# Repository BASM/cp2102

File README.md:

cp2102
======

 Silicon Laboratories CP2102 breakout board.

 Input mini-B, output 6 pins(SIL-6): 
 * 1 -- GND
 * 2 -- Vcc(5v),
 * 3 -- RX,
 * 4 -- TX,
 * 5 -- DTR, 
 * 6 -- RTS.

 Good for NXP LPC13xx ARM programming.

 Stage: work fine.

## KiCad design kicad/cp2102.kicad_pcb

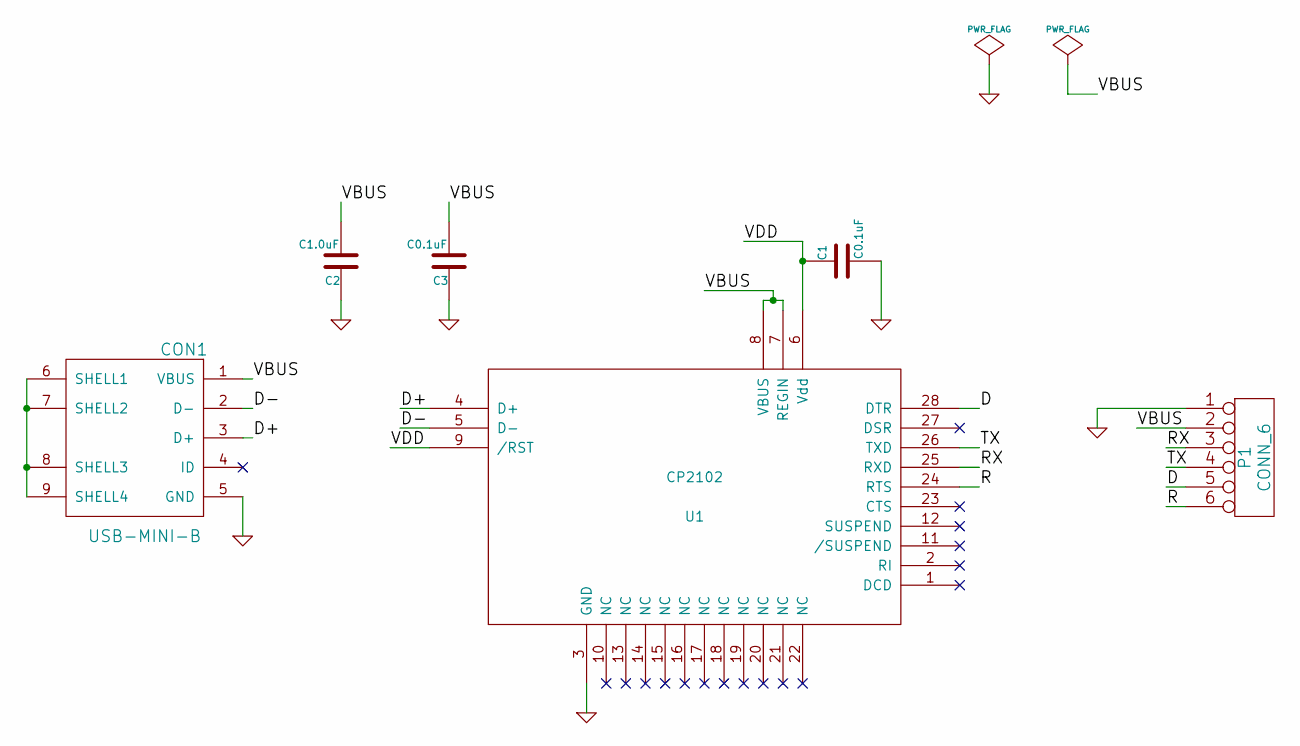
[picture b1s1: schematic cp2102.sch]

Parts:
C1, C3: C0.1uF
C2: C1.0uF
CON1: USB-MINI-B
P1: CONN_6
U1: CP2102

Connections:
/D: P1.5, U1.28 (DTR)
/D+: CON1.3 (D+), U1.4 (D+)
/D-: CON1.2 (D-), U1.5 (D-)
/R: P1.6, U1.24 (RTS)
/RX: P1.3, U1.25 (RXD)
/TX: P1.4, U1.26 (TXD)
/VBUS: C2.2, C3.2, CON1.1 (VBUS), P1.2, U1.7 (REGIN), U1.8 (VBUS)
/VDD: C1.1, U1.6 (Vdd), U1.9 (/RST)
GND: C1.2, C2.1, C3.1, CON1.5 (GND), P1.1, U1.3 (GND)
unnamed: CON1.6 (SHELL1), CON1.7 (SHELL2), CON1.8 (SHELL3), CON1.9 (SHELL4)

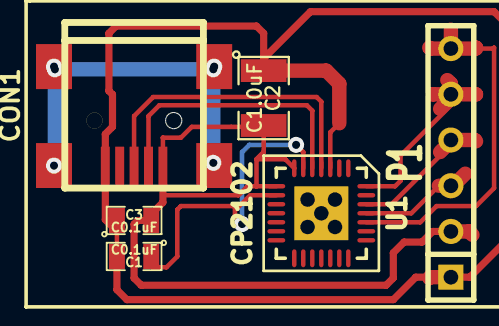
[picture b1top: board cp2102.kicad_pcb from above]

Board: 2 copper layers, 6 parts (0 on the bottom side), 10 nets.

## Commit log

2013-10-11 v0.1
2013-10-12 Swpan power pins.
2013-10-12 Some fix.
